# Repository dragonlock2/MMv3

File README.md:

# MMv3

MMv3 is the 3rd generation robot platform used to teach the IEEE Micromouse DeCal at UC Berkeley. It was designed with usability, manufacturability, size, and cost in mind.

## Setup

1. Follow the assembly instructions in [lab1](docs/lab1.md) using the latest **BOM** (see releases).
2. Plug mouse into your computer and upload the latest **firmware.uf2** (see releases) by dragging the file into the `RPI-RP2` folder that shows up. It should disappear and reappear as a `CIRCUITPY` folder.
    * If you've uploaded firmware before, you'll need to hold the `BOOTSEL` button on the Pi Pico while plugging in.
3. Download the latest CircuitPython [libraries](https://circuitpython.org/libraries) (for Version 7.x) and upload the following ones to the lib/ folder on your mouse.
    * adafruit_motor/
    * adafruit_onewire/
    * neopixel.mpy

## Labs

Skeleton lab code, lab documents, and solutions are stored in [labs/](labs/), [docs/](docs/), and [solutions/](solutions/), respectively. To get started with a lab, simply copy the contents of the folder over to the CircuitPython drive and edit files from there.

* [sanity](docs/sanity.md) - Hardware Check
* [lab1](docs/lab1.md) - Assembly and CircuitPython Basics
* [lab2](docs/lab2.md) - Encoders
* [lab3](docs/lab3.md) - IR Sensors
* [lab4](docs/lab4.md) - Odometry and Motor Control
* [lab5](docs/lab5.md) - Intro to PID
* [lab6](docs/lab6.md) - More PID
* [lab7](docs/lab7.md) - Maze Solving Primitives **(WIP)**
* lab8 - Flood Fill **(WIP)**

## Compiling CircuitPython

The DS28E05 1-Wire EEPROM operates at overdrive speeds only. Adding support involves compiling a patched version of CircuitPython.

1. Follow these [instructions](https://learn.adafruit.com/building-circuitpython/introduction) to get your system set up for compilation.
2. Follow these [instructions](https://learn.adafruit.com/building-circuitpython/build-circuitpython) to clone CircuitPython and do further setup but don't compile CircuitPython just yet.
3. Apply [circuitpython.patch](circuitpython.patch) using `patch -p1 < circuitpython.patch`
    * Also apply [macos.patch](macos.patch) if using MacOS.
4. Compile CircuitPython with `cd ports/raspberrypi && make  BOARD=raspberry_pi_pico`
5. Upload the resulting firmware.uf2!

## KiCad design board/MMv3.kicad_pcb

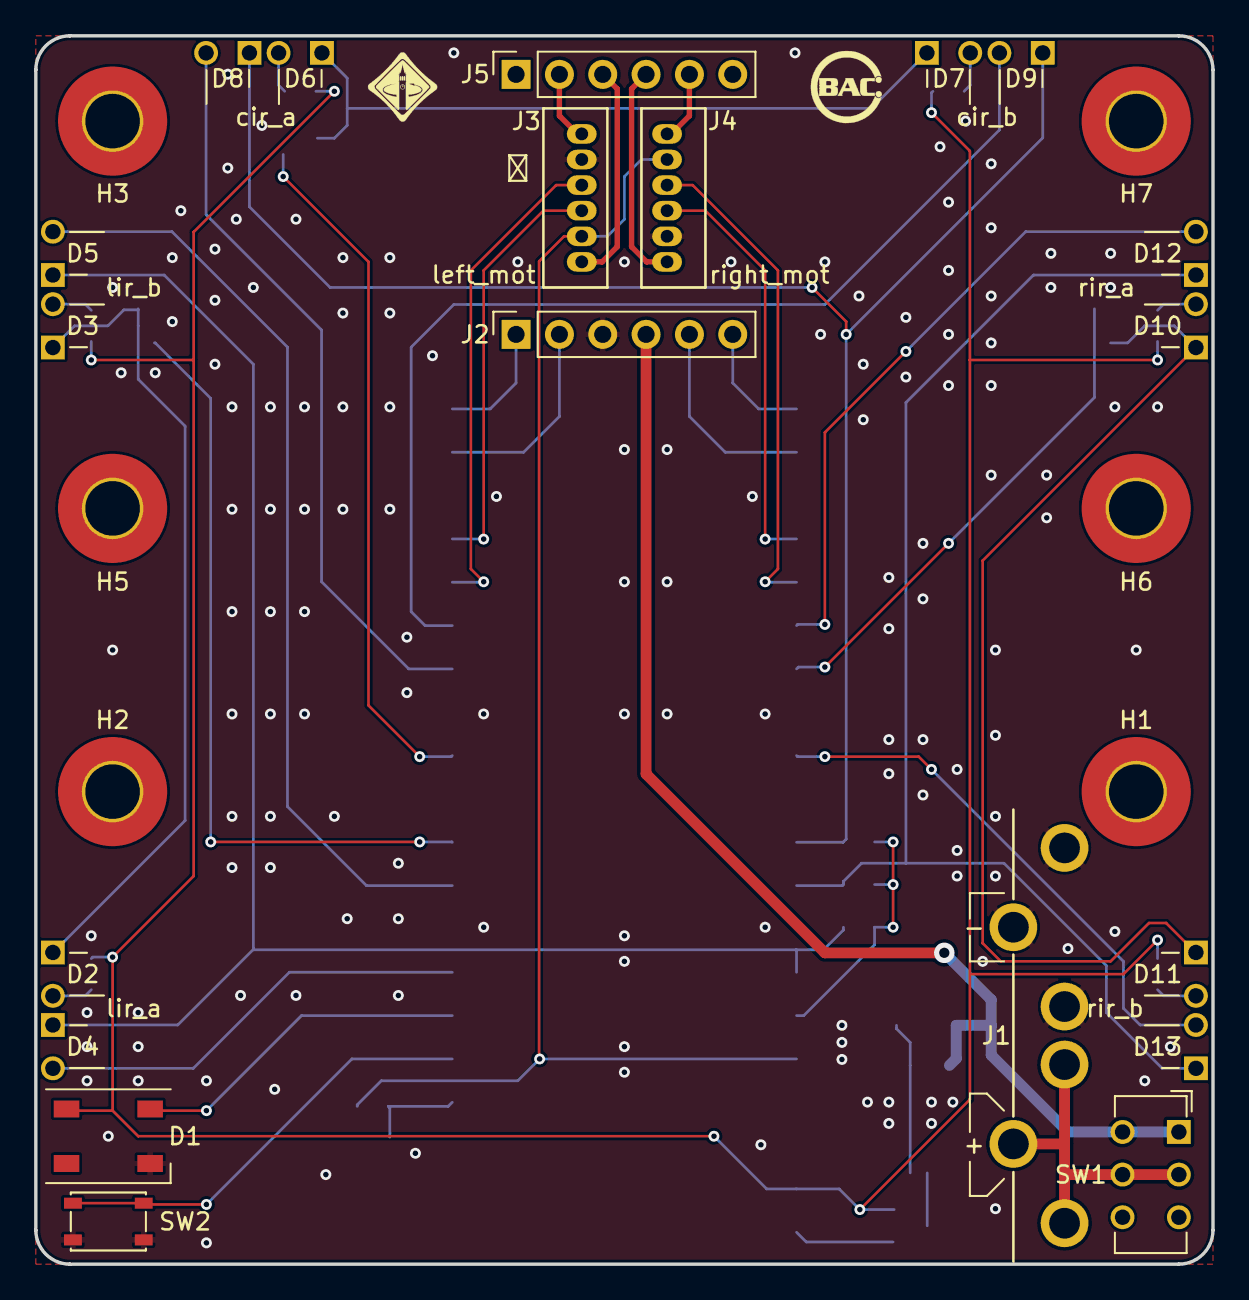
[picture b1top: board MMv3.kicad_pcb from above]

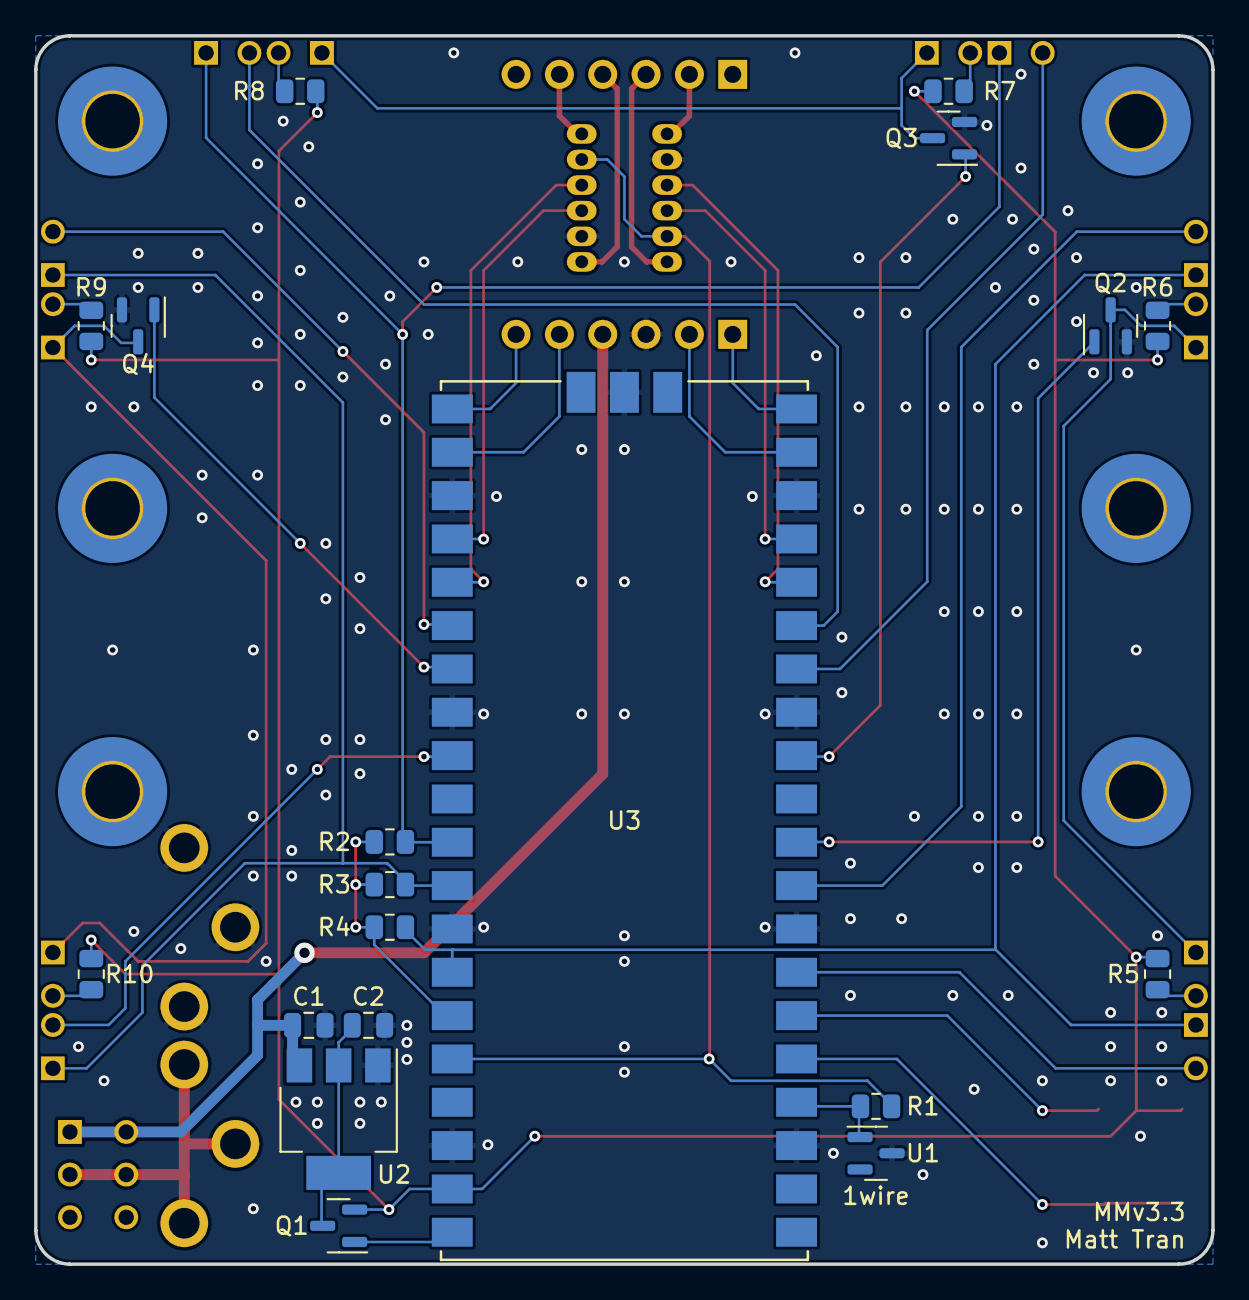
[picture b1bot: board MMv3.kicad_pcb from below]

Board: 2 copper layers, 69.0 x 72.0 mm, 47 parts (19 on the bottom side), 44 nets.

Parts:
C1, C2: 10u; C_0805_2012Metric
D1: WS2812B; LED_WS2812B_PLCC4_5.0x5.0mm_P3.2mm
D2, D3, D6, D7, D10, D11: LED; LED_D3.0mm_RH_THT_Clear
D4, D5, D8, D9, D12, D13: D_Photo_ALT; LED_D3.0mm_RH_THT_IRBlack
H1, H2, H3, H5, H6, H7: MountingHole; MountingHole_3.2mm_M3_Pad_TopBottom
H4: bac logo; bac_logo
H8: ieee logo; ieee_logo
J1: 9V; Keystone_593_594
J2: DRV8833_L; PinSocket_1x06_P2.54mm_Vertical
J3: left_mot; JST_ZH_Vert_6pin
J4: right_mot; JST_ZH_Vert_6pin
J5: DRV8833_R; PinSocket_1x06_P2.54mm_Vertical
Q1: DMG2301L; SOT-23
Q2, Q3, Q4: DMG2302U; SOT-23
R1: 1k; R_0805_2012Metric
R2, R3, R4: 10K; R_0805_2012Metric
R5, R6, R7, R8, R9, R10: 150; R_0805_2012Metric
SW1: PWR; SW_CuK_JS202011CQN_DPDT_Straight
SW2: but; SW_SPST_PTS810
U1: DS28E05R+T; SOT-23
U2: LD1117S50TR_SOT223; SOT-223-3_TabPin2
U3: RPi_Pico; RPi_Pico_SMD

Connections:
+3V3: J3.5, J4.5, R1.1, U3.36 (3V3)
+5V: D1.1 (VDD), Q1.2 (S), R5.1, R6.1, R7.1, R8.1, R9.1, R10.1, U3.39 (VSYS)
+9V: C1.1, J2.4, SW1.1 (A), SW1.4 (A), U2.3 (VI)
/+3V3A: R2.1, R3.1, R4.1, U3.35 (ADC_VREF)
/but: SW2.1 (A), U3.5 (GP3)
/c_adc: D8.1 (K), D9.1 (K), R2.2, U3.31 (GP26)
/cir_a: D8.2 (A), U3.14 (GP10)
/cir_b: D9.2 (A), U3.15 (GP11)
/cir_en: Q3.1 (G), U3.12 (GP9)
/l_adc: D4.1 (K), D5.1 (K), R4.2, U3.34 (GP28)
/lenc_a: J3.3, U3.16 (GP12)
/lenc_b: J3.4, U3.17 (GP13)
/lir_a: D4.2 (A), U3.7 (GP5)
/lir_b: D5.2 (A), U3.9 (GP6)
/lir_en: Q2.1 (G), U3.10 (GP7)
/lmot_in1: J2.6, U3.21 (GP16)
/lmot_in2: J2.5, U3.22 (GP17)
/lmot_m1: J3.1, J5.2
/lmot_m2: J3.6, J5.3
/neopixel: D1.4 (DIN), U3.6 (GP4)
/onewire: R1.2, U1.1 (DQ), U3.4 (GP2)
/r_adc: D12.1 (K), D13.1 (K), R3.2, U3.32 (GP27)
/renc_a: J4.3, U3.24 (GP18)
/renc_b: J4.4, U3.25 (GP19)
/rir_a: D12.2 (A), U3.26 (GP20)
/rir_b: D13.2 (A), U3.29 (GP22)
/rir_en: Q4.1 (G), U3.27 (GP21)
/rmot_in1: J2.2, U3.19 (GP14)
/rmot_in2: J2.1, U3.20 (GP15)
/rmot_m1: J4.1, J5.4
/rmot_m2: J4.6, J5.5
GND: C1.2, C2.2, D1.3 (VSS), J1.2, J2.3, J3.2, J4.2, Q2.2 (S), Q3.2 (S), Q4.2 (S), SW2.2 (B), U1.3 (GND), U2.1 (GND), U3.3 (GND), U3.8 (GND), U3.13 (GND), U3.18 (GND), U3.23 (GND), U3.28 (GND), U3.33 (GND), U3.38 (GND), U3.D2 (GND)
unnamed: C2.1, Q1.3 (D), U2.2 (VO)
unnamed: D2.1 (K), D3.1 (K), Q2.3 (D)
unnamed: D2.2 (A), R5.2
unnamed: D3.2 (A), R6.2
unnamed: D6.1 (K), D7.1 (K), Q3.3 (D)
unnamed: D6.2 (A), R7.2
unnamed: D7.2 (A), R8.2
unnamed: D10.1 (K), D11.1 (K), Q4.3 (D)
unnamed: D10.2 (A), R9.2
unnamed: D11.2 (A), R10.2
unnamed: J1.1, SW1.2 (B), SW1.5 (B)
VBUS: Q1.1 (G), U3.40 (VBUS)

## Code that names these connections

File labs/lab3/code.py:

import board
import ulab.numpy as np

from irsensor import IRSensors

""" Peripherals """

# IR sensors
ir = IRSensors(
    board.GP7,  board.GP5,  board.GP6,  board.GP28, # left
    board.GP9,  board.GP10, board.GP11, board.GP26, # center
    board.GP21, board.GP20, board.GP22, board.GP27  # right
)

""" Main """

MAX_DIST = 60 # mm
STEP = 10 # mm

def lstsq(A, b):
    At = A.transpose()
    return np.dot(np.dot(np.linalg.inv(np.dot(At, A)), At), b)

def calibrate(a, b):
    x_a, d_a, x_b, d_b = [], [], [], []
    for d in np.arange(0, MAX_DIST+1e-3, STEP):
        print("Place wall at", d, "\bmm and press <enter> to record", end="")
        input()
        ir.scan()
        d_a.append(d); d_b.append(d)
        x_a.append(getattr(ir, a)); x_b.append(getattr(ir, b))

    A_a = np.concatenate((
        np.array(x_a).reshape((len(x_a),1)),
        np.ones(len(x_a)).reshape((len(x_a),1))
    ), axis=1)
    d_a = np.array(d_a)

    A_b = np.concatenate((
        np.array(x_b).reshape((len(x_b),1)),
        np.ones(len(x_b)).reshape((len(x_b),1))
    ), axis=1)
    d_b = np.array(d_b)

    return lstsq(A_a, d_a), lstsq(A_b, d_b)

if __name__ == "__main__":
    print("Calibrating left sensors...")
    k_a, k_b = calibrate("lir_a", "lir_b")
    print()
    print("lir_a constants:", "a =", k_a[0], "\tb =", k_a[1])
    print("lir_b constants:", "a =", k_b[0], "\tb =", k_b[1])
    print()

    print("Calibrating center sensors...")
    k_a, k_b = calibrate("cir_a", "cir_b")
    print()
    print("cir_a constants:", "a =", k_a[0], "\tb =", k_a[1])
    print("cir_b constants:", "a =", k_b[0], "\tb =", k_b[1])
    print()

    print("Calibrating right sensors...")
    k_a, k_b = calibrate("rir_a", "rir_b")
    print()
    print("rir_a constants:", "a =", k_a[0], "\tb =", k_a[1])
    print("rir_b constants:", "a =", k_b[0], "\tb =", k_b[1])
    print()

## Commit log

2021-06-27 created board project
2021-06-28 Finished schematic
2021-06-28 Finished layout
2021-06-28 Fixed SWD pinout
2021-07-18 Added some test code
2021-07-20 Added DS28E05 support
2021-07-20 added basic going straight code
2021-10-12 finished mmv3.1 routing
2021-10-12 finished MMv3.1 layout
2021-10-27 updated pinout to MMv3.1
2021-10-29 Refactor
2021-10-29 Added serial instructions
2021-10-29 finished sanity lab
2021-10-31 add patch for macos compilation
2021-11-01 fixed 1wire for circuitpython
2021-11-01 write model number to eeprom
2021-12-03 finished MMv3.2
2021-12-04 finished lab 1 coding
2021-12-05 finished lab2
2021-12-05 fix centering
2021-12-05 fix code
2021-12-05 started lab3 doc
2021-12-05 added outline for labs
2021-12-05 finished lab4
2021-12-05 finished lab5
2021-12-05 working on lab 6
2021-12-13 updated readmes
2021-12-13 progress on lab 3
2021-12-22 updated lab 1
2021-12-23 finished lab 3
2021-12-24 finished lab 6
2021-12-31 convert to kicad 6
2021-12-31 update lib
2022-01-08 adapt to BAC standard capability
2022-02-26 commented out 1wire code
2023-11-18 add MMv2 and MMSim as archive projects
